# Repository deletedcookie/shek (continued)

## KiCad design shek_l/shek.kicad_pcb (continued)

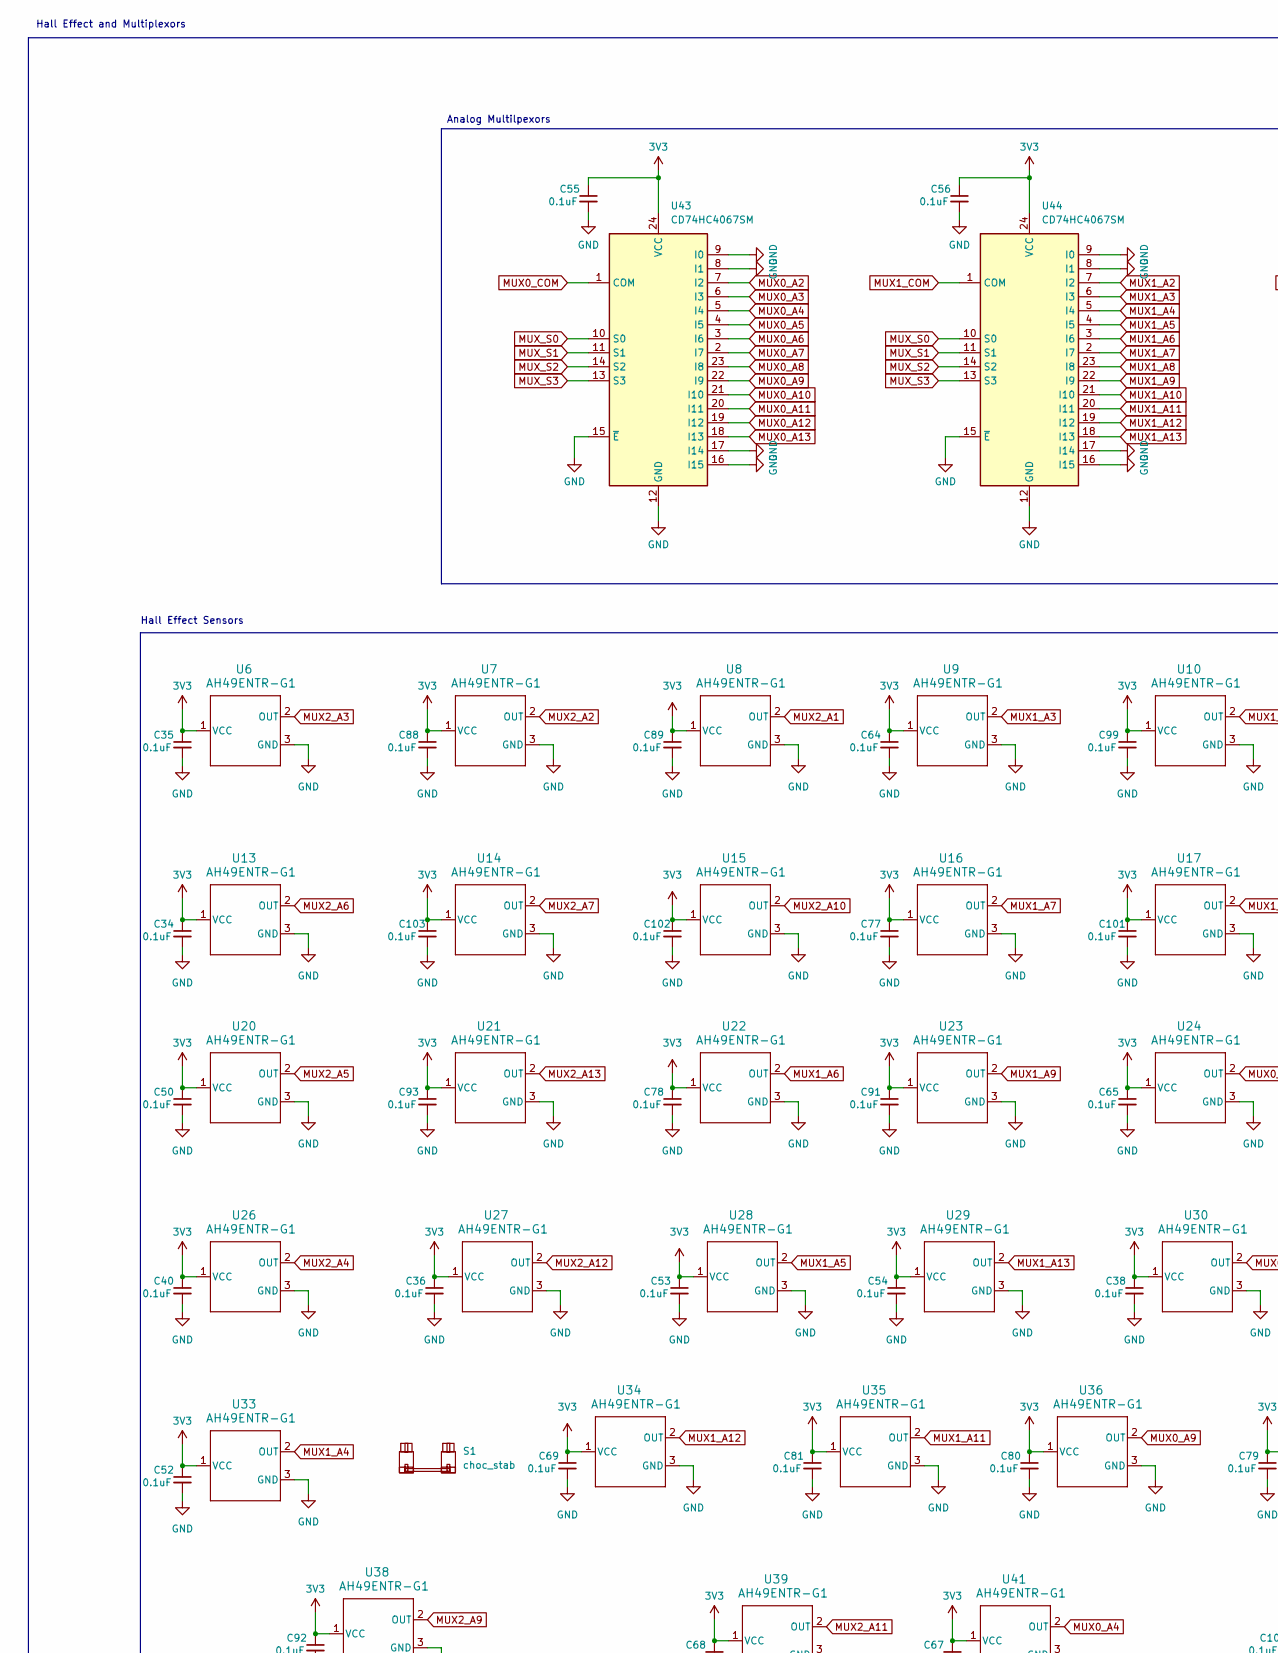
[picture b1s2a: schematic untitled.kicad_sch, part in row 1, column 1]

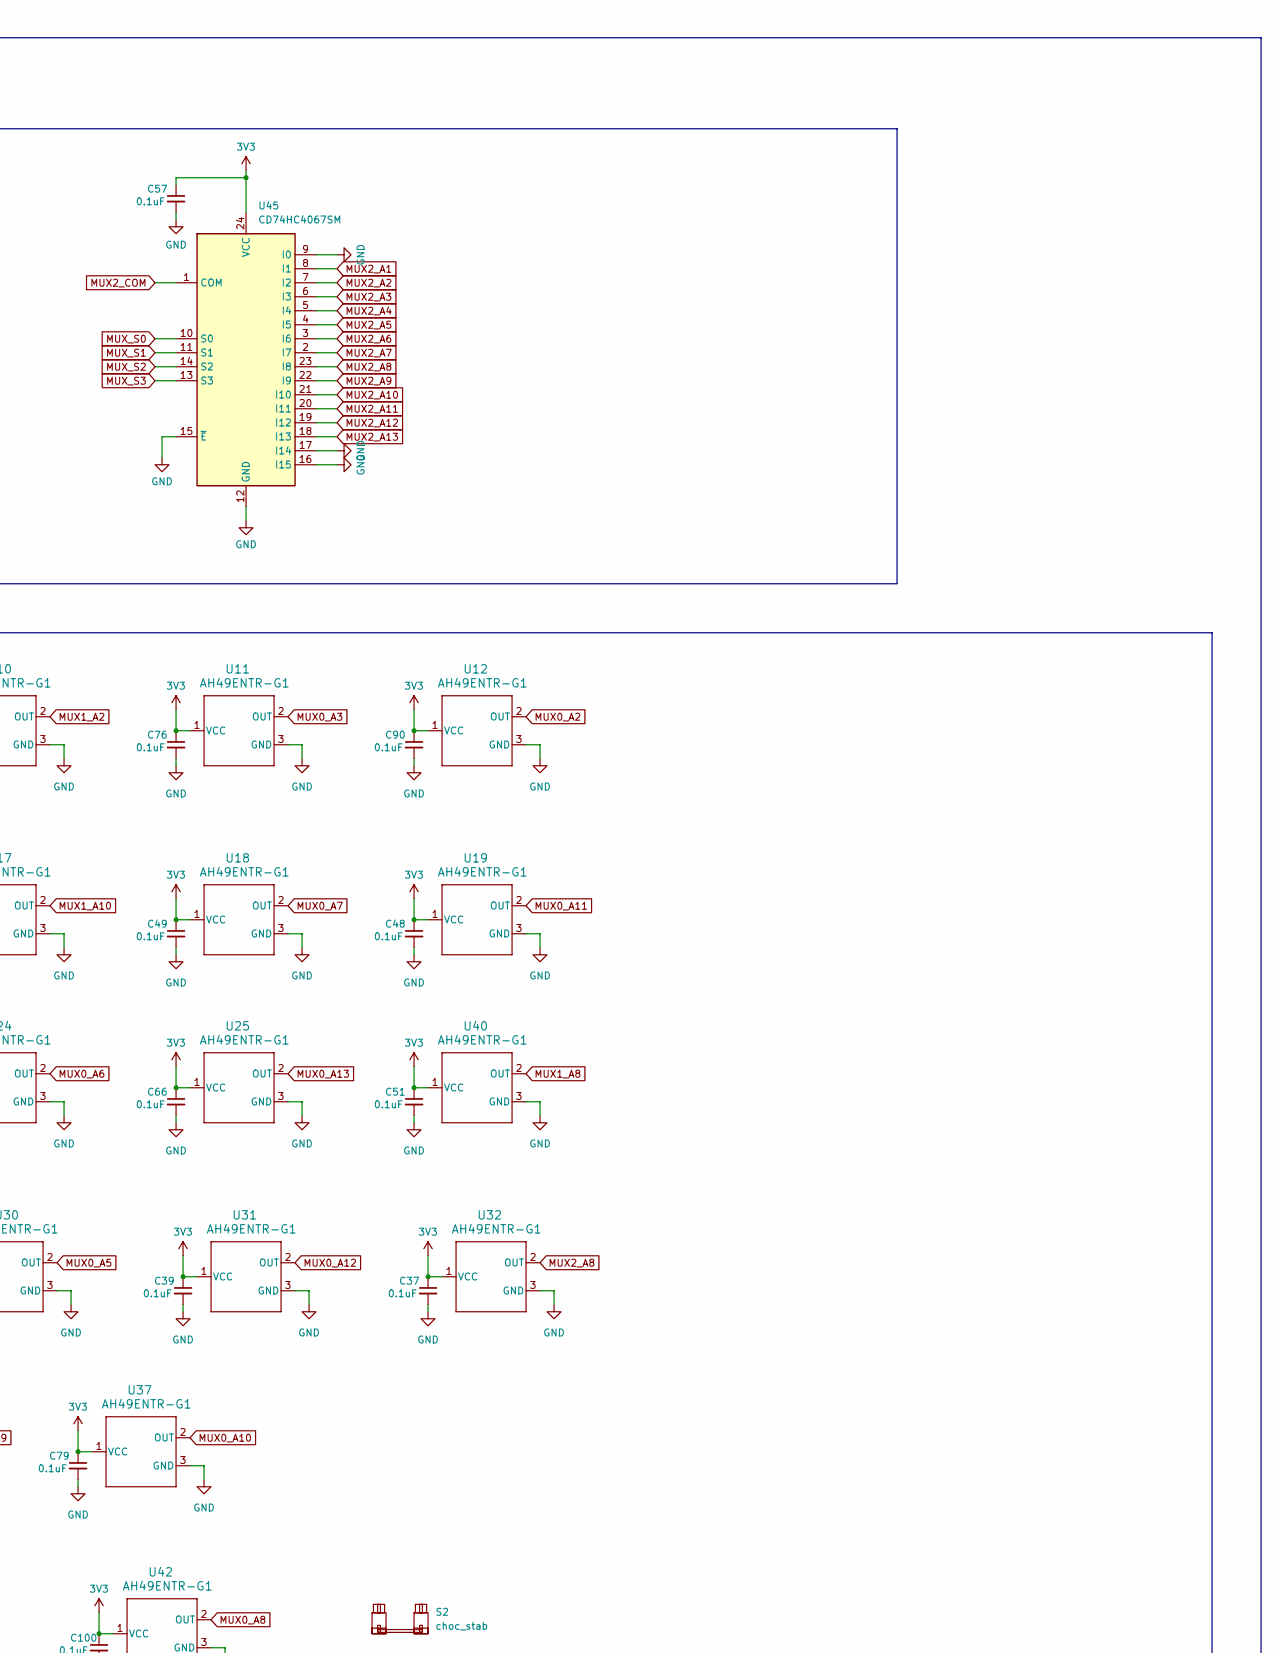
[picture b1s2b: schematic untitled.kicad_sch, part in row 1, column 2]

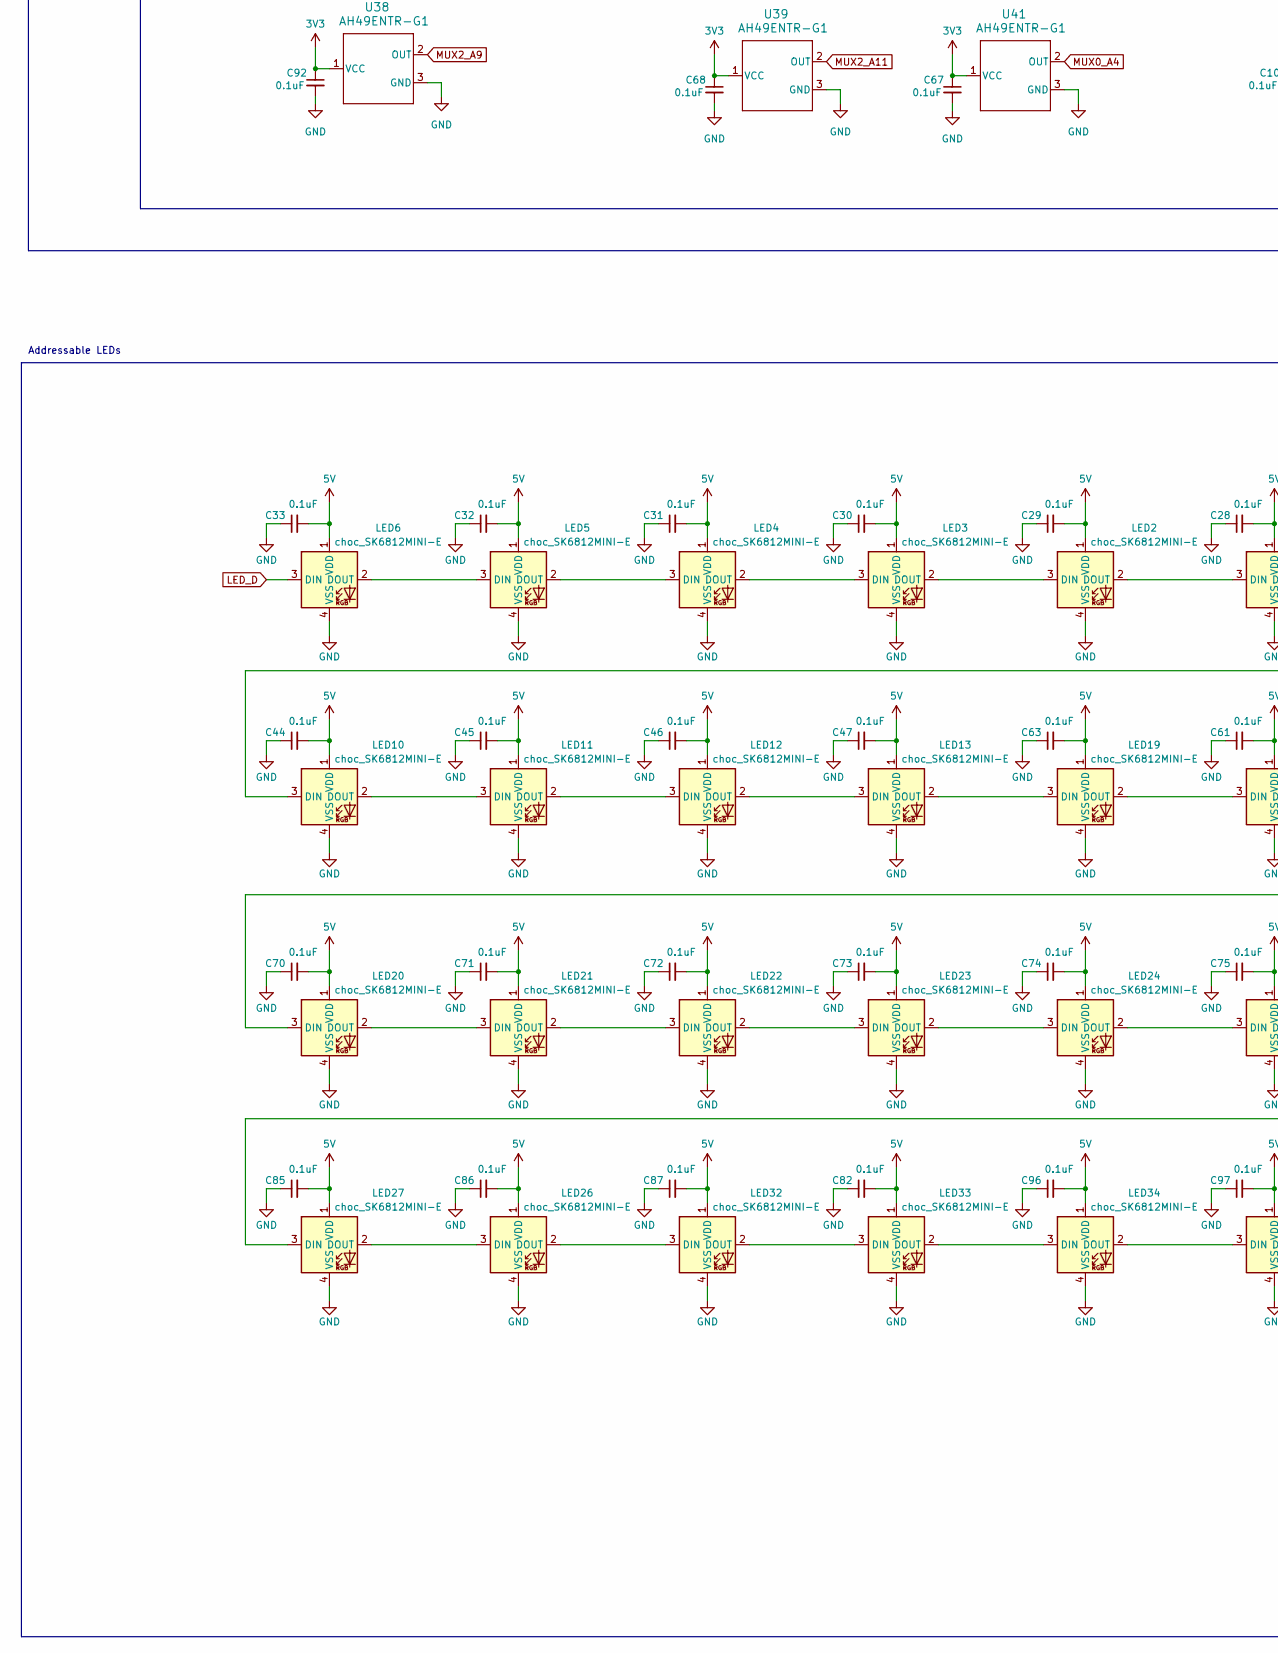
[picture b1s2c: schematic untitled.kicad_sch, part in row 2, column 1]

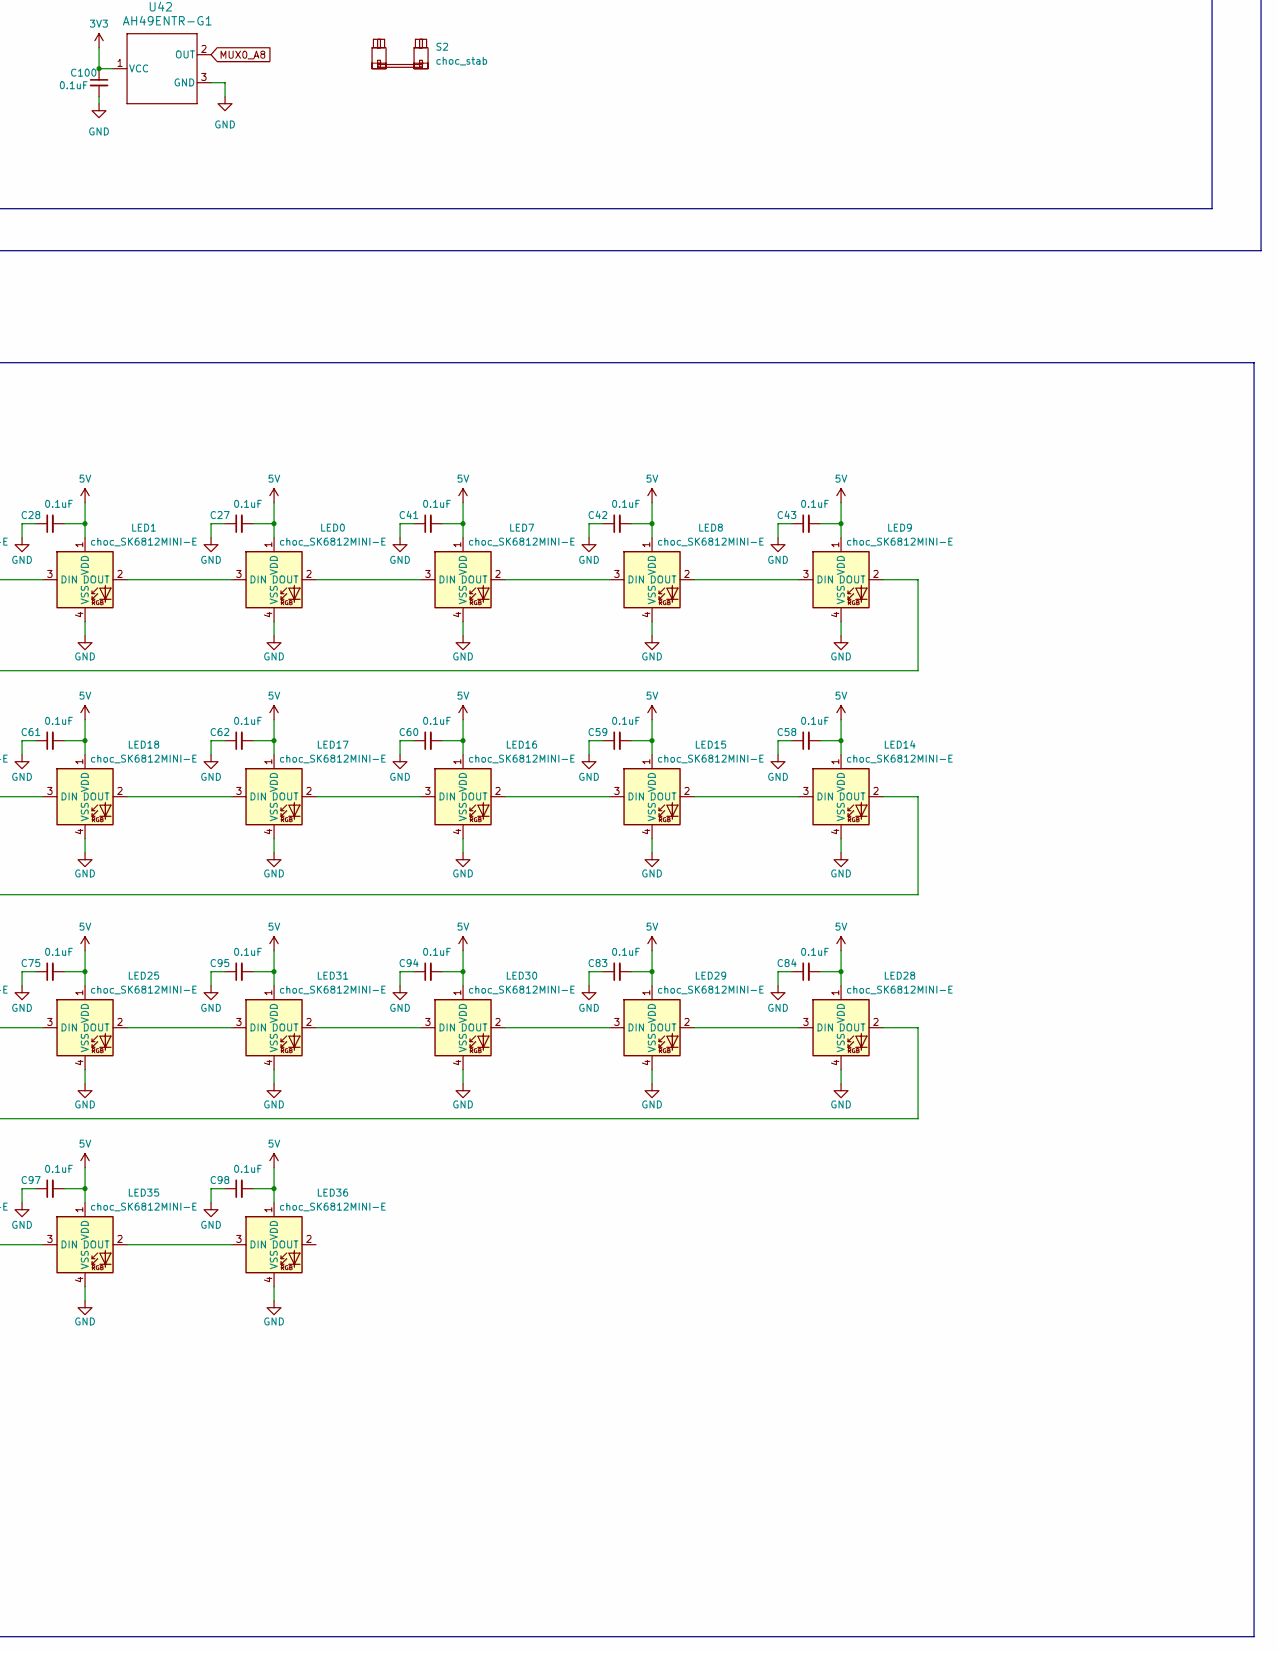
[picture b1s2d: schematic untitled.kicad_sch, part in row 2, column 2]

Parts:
C27, C28, C29, C30, C31, C32, C33, C34, C35, C36, C37, C38, C39, C40, C41, C42, C43, C44, C45, C46, C47, C48, C49, C50, C51, C52, C53, C54, C55, C56, C57, C58, C59, C60, C61, C62, C63, C64, C65, C66, C67, C68, C69, C70, C71, C72, C73, C74, C75, C76, C77, C78, C79, C80, C81, C82, C83, C84, C85, C86, C87, C88, C89, C90, C91, C92, C93, C94, C95, C96, C97, C98, C99, C100, C101, C102, C103: 0.1uF; C_0603_1608Metric; Digikey 311-1088-1-ND
LED0, LED1, LED2, LED3, LED4, LED5, LED6, LED7, LED8, LED9, LED10, LED11, LED12, LED13, LED14, LED15, LED16, LED17, LED18, LED19, LED20, LED21, LED22, LED23, LED24, LED25, LED26, LED27, LED28, LED29, LED30, LED31, LED32, LED33, LED34, LED35, LED36: choc_SK6812MINI-E; LED_choc_6028R
S1, S2: choc_stab; Stabilizers_Plate-Mounted_2U
U6, U7, U8, U9, U10, U11, U12, U13, U14, U15, U16, U17, U18, U19, U21, U22, U23, U24, U25, U27, U28, U29, U30, U31, U32, U33, U34, U35, U36, U37, U39, U40, U42: AH49ENTR-G1; SOT-23-3_ChocV2-1U; Digikey AH49ENTR-G1DICT-ND
U20, U38: AH49ENTR-G1; SOT-23-3_ChocV2-1.5U; Digikey AH49ENTR-G1DICT-ND
U26: AH49ENTR-G1; SOT-23-3_ChocV2-1.75U; Digikey AH49ENTR-G1DICT-ND
U41: AH49ENTR-G1; SOT-23-3_ChocV2-1.25U; Digikey AH49ENTR-G1DICT-ND
U43, U44, U45: CD74HC4067SM; SSOP-24_5.3x8.2mm_P0.65mm; Digikey 1727-2807-1-ND

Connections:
3V3: C34.1, C35.1, C36.1, C37.1, C38.1, C39.1, C40.1, C48.1, C49.1, C50.1, C51.1, C52.1, C53.1, C54.1, C55.1, C56.1, C57.1, C64.1, C65.1, C66.1, C67.1, C68.1, C69.1, C76.1, C77.1, C78.1, C79.1, C80.1, C81.1, C88.1, C89.1, C90.1, C91.1, C92.1, C93.1, C99.1, C100.1, C101.1, C102.1, C103.1, U6.1 (VCC), U7.1 (VCC), U8.1 (VCC), U9.1 (VCC), U10.1 (VCC), U11.1 (VCC), U12.1 (VCC), U13.1 (VCC), U14.1 (VCC), U15.1 (VCC), U16.1 (VCC), U17.1 (VCC), U18.1 (VCC), U19.1 (VCC), U20.1 (VCC), U21.1 (VCC), U22.1 (VCC), U23.1 (VCC), U24.1 (VCC), U25.1 (VCC), U26.1 (VCC), U27.1 (VCC), U28.1 (VCC), U29.1 (VCC), U30.1 (VCC), U31.1 (VCC), U32.1 (VCC), U33.1 (VCC), U34.1 (VCC), U35.1 (VCC), U36.1 (VCC), U37.1 (VCC), U38.1 (VCC), U39.1 (VCC), U40.1 (VCC), U41.1 (VCC), U42.1 (VCC), U43.24 (VCC), U44.24 (VCC), U45.24 (VCC); also elsewhere on the board
5V: C27.2, C28.2, C29.2, C30.2, C31.2, C32.2, C33.2, C41.2, C42.2, C43.2, C44.2, C45.2, C46.2, C47.2, C58.2, C59.2, C60.2, C61.2, C62.2, C63.2, C70.2, C71.2, C72.2, C73.2, C74.2, C75.2, C82.2, C83.2, C84.2, C85.2, C86.2, C87.2, C94.2, C95.2, C96.2, C97.2, C98.2, LED0.1 (VDD), LED1.1 (VDD), LED2.1 (VDD), LED3.1 (VDD), LED4.1 (VDD), LED5.1 (VDD), LED6.1 (VDD), LED7.1 (VDD), LED8.1 (VDD), LED9.1 (VDD), LED10.1 (VDD), LED11.1 (VDD), LED12.1 (VDD), LED13.1 (VDD), LED14.1 (VDD), LED15.1 (VDD), LED16.1 (VDD), LED17.1 (VDD), LED18.1 (VDD), LED19.1 (VDD), LED20.1 (VDD), LED21.1 (VDD), LED22.1 (VDD), LED23.1 (VDD), LED24.1 (VDD), LED25.1 (VDD), LED26.1 (VDD), LED27.1 (VDD), LED28.1 (VDD), LED29.1 (VDD), LED30.1 (VDD), LED31.1 (VDD), LED32.1 (VDD), LED33.1 (VDD), LED34.1 (VDD), LED35.1 (VDD), LED36.1 (VDD); also elsewhere on the board
GND: C27.1, C28.1, C29.1, C30.1, C31.1, C32.1, C33.1, C34.2, C35.2, C36.2, C37.2, C38.2, C39.2, C40.2, C41.1, C42.1, C43.1, C44.1, C45.1, C46.1, C47.1, C48.2, C49.2, C50.2, C51.2, C52.2, C53.2, C54.2, C55.2, C56.2, C57.2, C58.1, C59.1, C60.1, C61.1, C62.1, C63.1, C64.2, C65.2, C66.2, C67.2, C68.2, C69.2, C70.1, C71.1, C72.1, C73.1, C74.1, C75.1, C76.2, C77.2, C78.2, C79.2, C80.2, C81.2, C82.1, C83.1, C84.1, C85.1, C86.1, C87.1, C88.2, C89.2, C90.2, C91.2, C92.2, C93.2, C94.1, C95.1, C96.1, C97.1, C98.1, C99.2, C100.2, C101.2, C102.2, C103.2, LED0.4 (VSS), LED1.4 (VSS), LED2.4 (VSS), LED3.4 (VSS), LED4.4 (VSS), LED5.4 (VSS), LED6.4 (VSS), LED7.4 (VSS), LED8.4 (VSS), LED9.4 (VSS), LED10.4 (VSS), LED11.4 (VSS), LED12.4 (VSS), LED13.4 (VSS), LED14.4 (VSS), LED15.4 (VSS), LED16.4 (VSS), LED17.4 (VSS), LED18.4 (VSS), LED19.4 (VSS), LED20.4 (VSS), LED21.4 (VSS), LED22.4 (VSS), LED23.4 (VSS), LED24.4 (VSS), LED25.4 (VSS), LED26.4 (VSS), LED27.4 (VSS), LED28.4 (VSS), LED29.4 (VSS), LED30.4 (VSS), LED31.4 (VSS), LED32.4 (VSS), LED33.4 (VSS), LED34.4 (VSS), LED35.4 (VSS), LED36.4 (VSS), U6.3 (GND), U7.3 (GND), U8.3 (GND), U9.3 (GND), U10.3 (GND), U11.3 (GND), U12.3 (GND), U13.3 (GND), U14.3 (GND), U15.3 (GND), U16.3 (GND), U17.3 (GND), U18.3 (GND), U19.3 (GND), U20.3 (GND), U21.3 (GND), U22.3 (GND), U23.3 (GND), U24.3 (GND), U25.3 (GND), U26.3 (GND), U27.3 (GND), U28.3 (GND), U29.3 (GND), U30.3 (GND), U31.3 (GND), U32.3 (GND), U33.3 (GND), U34.3 (GND), U35.3 (GND), U36.3 (GND), U37.3 (GND), U38.3 (GND), U39.3 (GND), U40.3 (GND), U41.3 (GND), U42.3 (GND), U43.8 (I1), U43.9 (I0), U43.12 (GND), U43.15 (~E), U43.16 (I15), U43.17 (I14), U44.8 (I1), U44.9 (I0), U44.12 (GND), U44.15 (~E), U44.16 (I15), U44.17 (I14), U45.9 (I0), U45.12 (GND), U45.15 (~E), U45.16 (I15), U45.17 (I14); also elsewhere on the board
LED_D: LED6.3 (DIN); also elsewhere on the board
MUX0_A2: U12.2 (OUT), U43.7 (I2)
MUX0_A3: U11.2 (OUT), U43.6 (I3)
MUX0_A4: U41.2 (OUT), U43.5 (I4)
MUX0_A5: U30.2 (OUT), U43.4 (I5)
MUX0_A6: U24.2 (OUT), U43.3 (I6)
MUX0_A7: U18.2 (OUT), U43.2 (I7)
MUX0_A8: U42.2 (OUT), U43.23 (I8)
MUX0_A9: U36.2 (OUT), U43.22 (I9)
MUX0_A10: U37.2 (OUT), U43.21 (I10)
MUX0_A11: U19.2 (OUT), U43.20 (I11)
MUX0_A12: U31.2 (OUT), U43.19 (I12)
MUX0_A13: U25.2 (OUT), U43.18 (I13)
MUX0_COM: U43.1 (COM); also elsewhere on the board
MUX1_A2: U10.2 (OUT), U44.7 (I2)
MUX1_A3: U9.2 (OUT), U44.6 (I3)
MUX1_A4: U33.2 (OUT), U44.5 (I4)
MUX1_A5: U28.2 (OUT), U44.4 (I5)
MUX1_A6: U22.2 (OUT), U44.3 (I6)
MUX1_A7: U16.2 (OUT), U44.2 (I7)
MUX1_A8: U40.2 (OUT), U44.23 (I8)
MUX1_A9: U23.2 (OUT), U44.22 (I9)
MUX1_A10: U17.2 (OUT), U44.21 (I10)
MUX1_A11: U35.2 (OUT), U44.20 (I11)
MUX1_A12: U34.2 (OUT), U44.19 (I12)
MUX1_A13: U29.2 (OUT), U44.18 (I13)
MUX1_COM: U44.1 (COM); also elsewhere on the board
MUX2_A1: U8.2 (OUT), U45.8 (I1)
MUX2_A2: U7.2 (OUT), U45.7 (I2)
MUX2_A3: U6.2 (OUT), U45.6 (I3)
MUX2_A4: U26.2 (OUT), U45.5 (I4)
MUX2_A5: U20.2 (OUT), U45.4 (I5)
MUX2_A6: U13.2 (OUT), U45.3 (I6)
MUX2_A7: U14.2 (OUT), U45.2 (I7)
MUX2_A8: U32.2 (OUT), U45.23 (I8)
MUX2_A9: U38.2 (OUT), U45.22 (I9)
MUX2_A10: U15.2 (OUT), U45.21 (I10)
MUX2_A11: U39.2 (OUT), U45.20 (I11)
MUX2_A12: U27.2 (OUT), U45.19 (I12)
MUX2_A13: U21.2 (OUT), U45.18 (I13)
MUX2_COM: U45.1 (COM); also elsewhere on the board
MUX_S0: U43.10 (S0), U44.10 (S0), U45.10 (S0); also elsewhere on the board
MUX_S1: U43.11 (S1), U44.11 (S1), U45.11 (S1); also elsewhere on the board
MUX_S2: U43.14 (S2), U44.14 (S2), U45.14 (S2); also elsewhere on the board
MUX_S3: U43.13 (S3), U44.13 (S3), U45.13 (S3); also elsewhere on the board
unnamed: LED5.3 (DIN), LED6.2 (DOUT)
unnamed: LED4.3 (DIN), LED5.2 (DOUT)
unnamed: LED3.3 (DIN), LED4.2 (DOUT)
unnamed: LED2.3 (DIN), LED3.2 (DOUT)
unnamed: LED1.3 (DIN), LED2.2 (DOUT)
unnamed: LED0.3 (DIN), LED1.2 (DOUT)
unnamed: LED0.2 (DOUT), LED7.3 (DIN)
unnamed: LED7.2 (DOUT), LED8.3 (DIN)
unnamed: LED8.2 (DOUT), LED9.3 (DIN)
unnamed: LED9.2 (DOUT), LED10.3 (DIN)
unnamed: LED10.2 (DOUT), LED11.3 (DIN)
unnamed: LED11.2 (DOUT), LED12.3 (DIN)
unnamed: LED12.2 (DOUT), LED13.3 (DIN)
unnamed: LED13.2 (DOUT), LED19.3 (DIN)
unnamed: LED18.3 (DIN), LED19.2 (DOUT)
unnamed: LED17.3 (DIN), LED18.2 (DOUT)
unnamed: LED16.3 (DIN), LED17.2 (DOUT)
unnamed: LED15.3 (DIN), LED16.2 (DOUT)
unnamed: LED14.3 (DIN), LED15.2 (DOUT)
unnamed: LED14.2 (DOUT), LED20.3 (DIN)
unnamed: LED20.2 (DOUT), LED21.3 (DIN)
unnamed: LED21.2 (DOUT), LED22.3 (DIN)
unnamed: LED22.2 (DOUT), LED23.3 (DIN)
unnamed: LED23.2 (DOUT), LED24.3 (DIN)
unnamed: LED24.2 (DOUT), LED25.3 (DIN)
unnamed: LED25.2 (DOUT), LED31.3 (DIN)
unnamed: LED30.3 (DIN), LED31.2 (DOUT)
unnamed: LED29.3 (DIN), LED30.2 (DOUT)
unnamed: LED28.3 (DIN), LED29.2 (DOUT)
unnamed: LED27.3 (DIN), LED28.2 (DOUT)
unnamed: LED26.3 (DIN), LED27.2 (DOUT)
unnamed: LED26.2 (DOUT), LED32.3 (DIN)
unnamed: LED32.2 (DOUT), LED33.3 (DIN)
unnamed: LED33.2 (DOUT), LED34.3 (DIN)
unnamed: LED34.2 (DOUT), LED35.3 (DIN)
unnamed: LED35.2 (DOUT), LED36.3 (DIN)

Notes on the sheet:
Hall Effect and Multiplexors
Analog Multilpexors
Addressable LEDs
Hall Effect Sensors

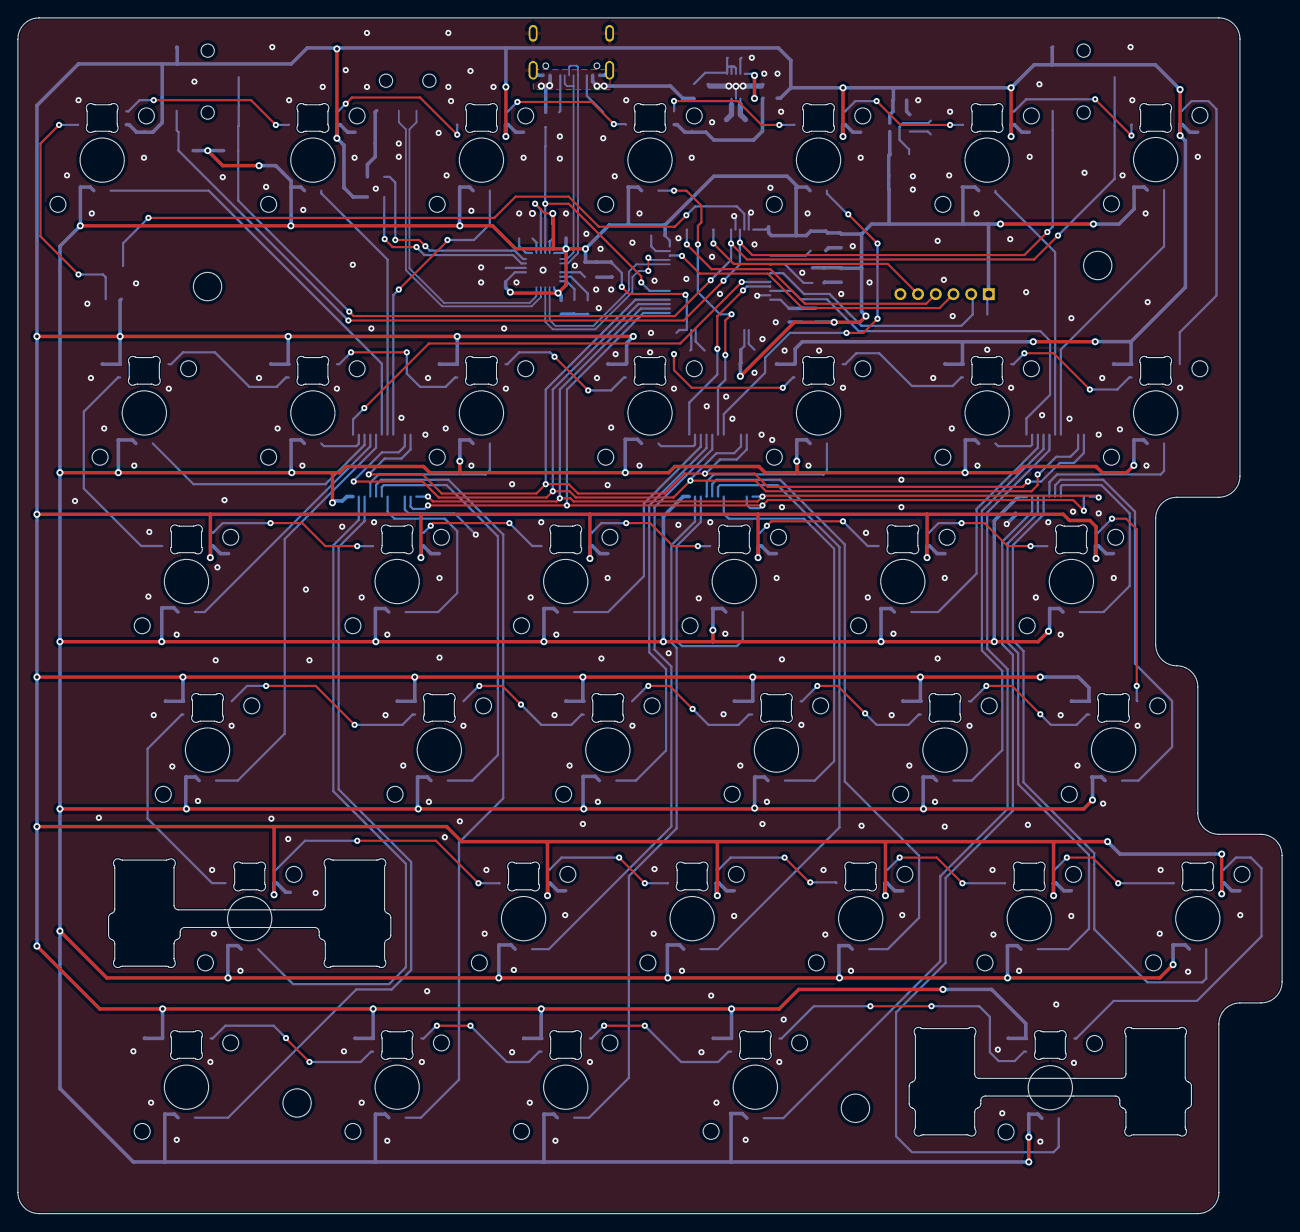
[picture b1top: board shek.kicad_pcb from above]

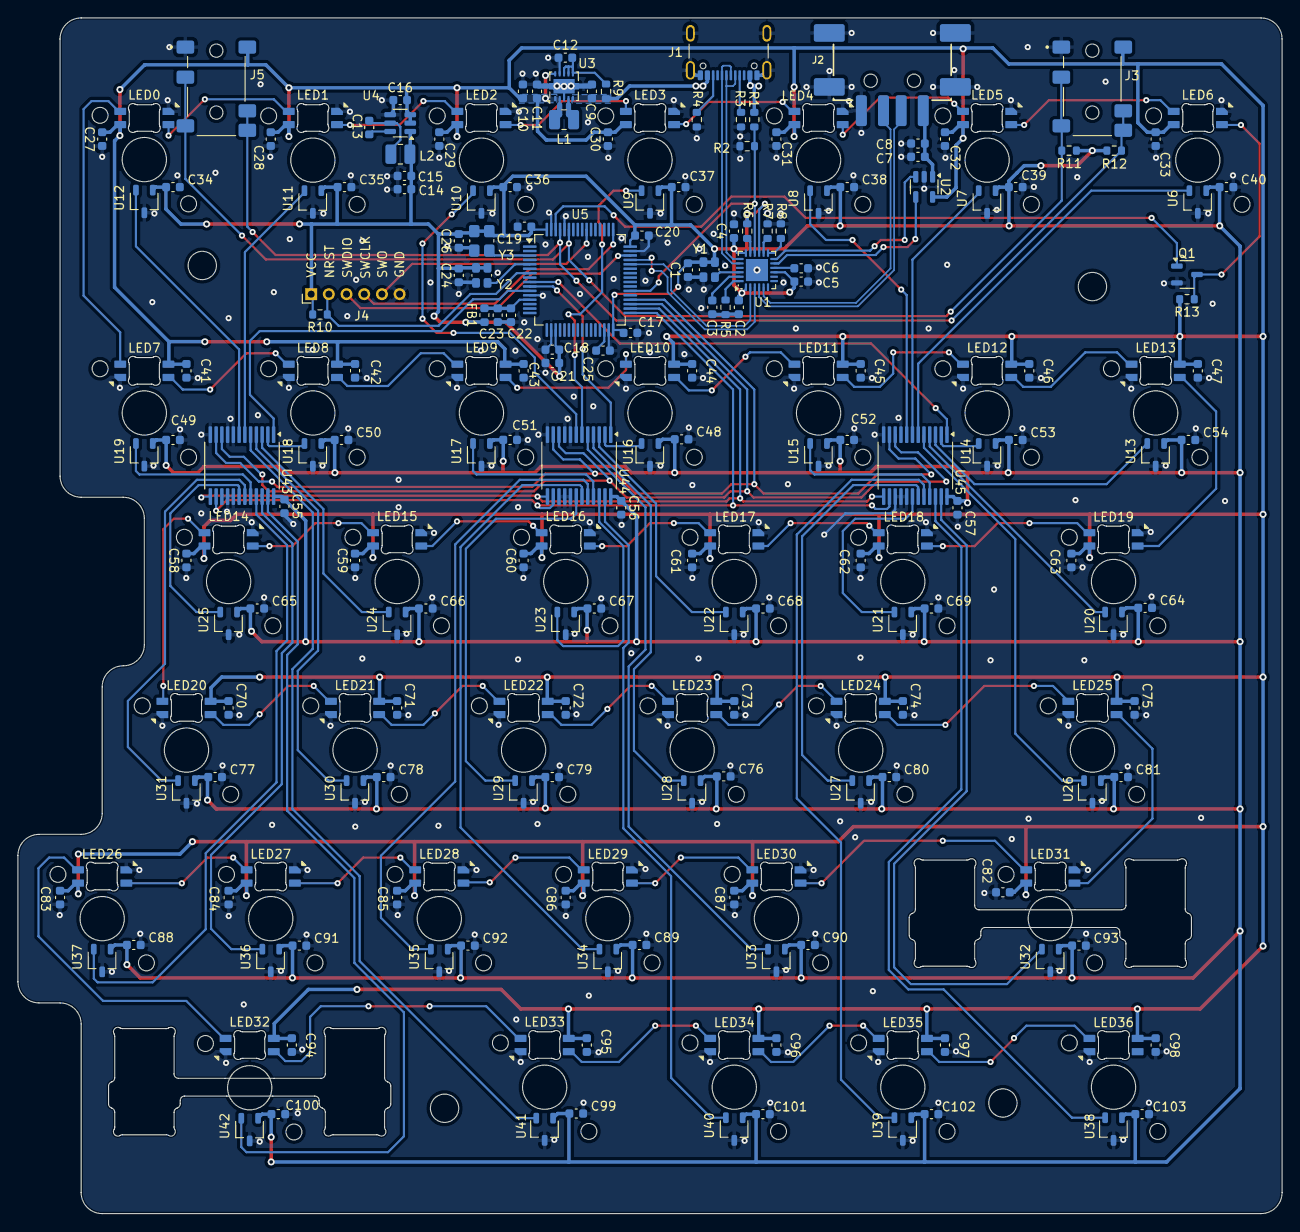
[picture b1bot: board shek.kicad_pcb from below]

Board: 2 copper layers, 142.9 x 135.1 mm, 216 parts (173 on the bottom side), 120 nets.

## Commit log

2025-09-28 spreedsheet to help with config
